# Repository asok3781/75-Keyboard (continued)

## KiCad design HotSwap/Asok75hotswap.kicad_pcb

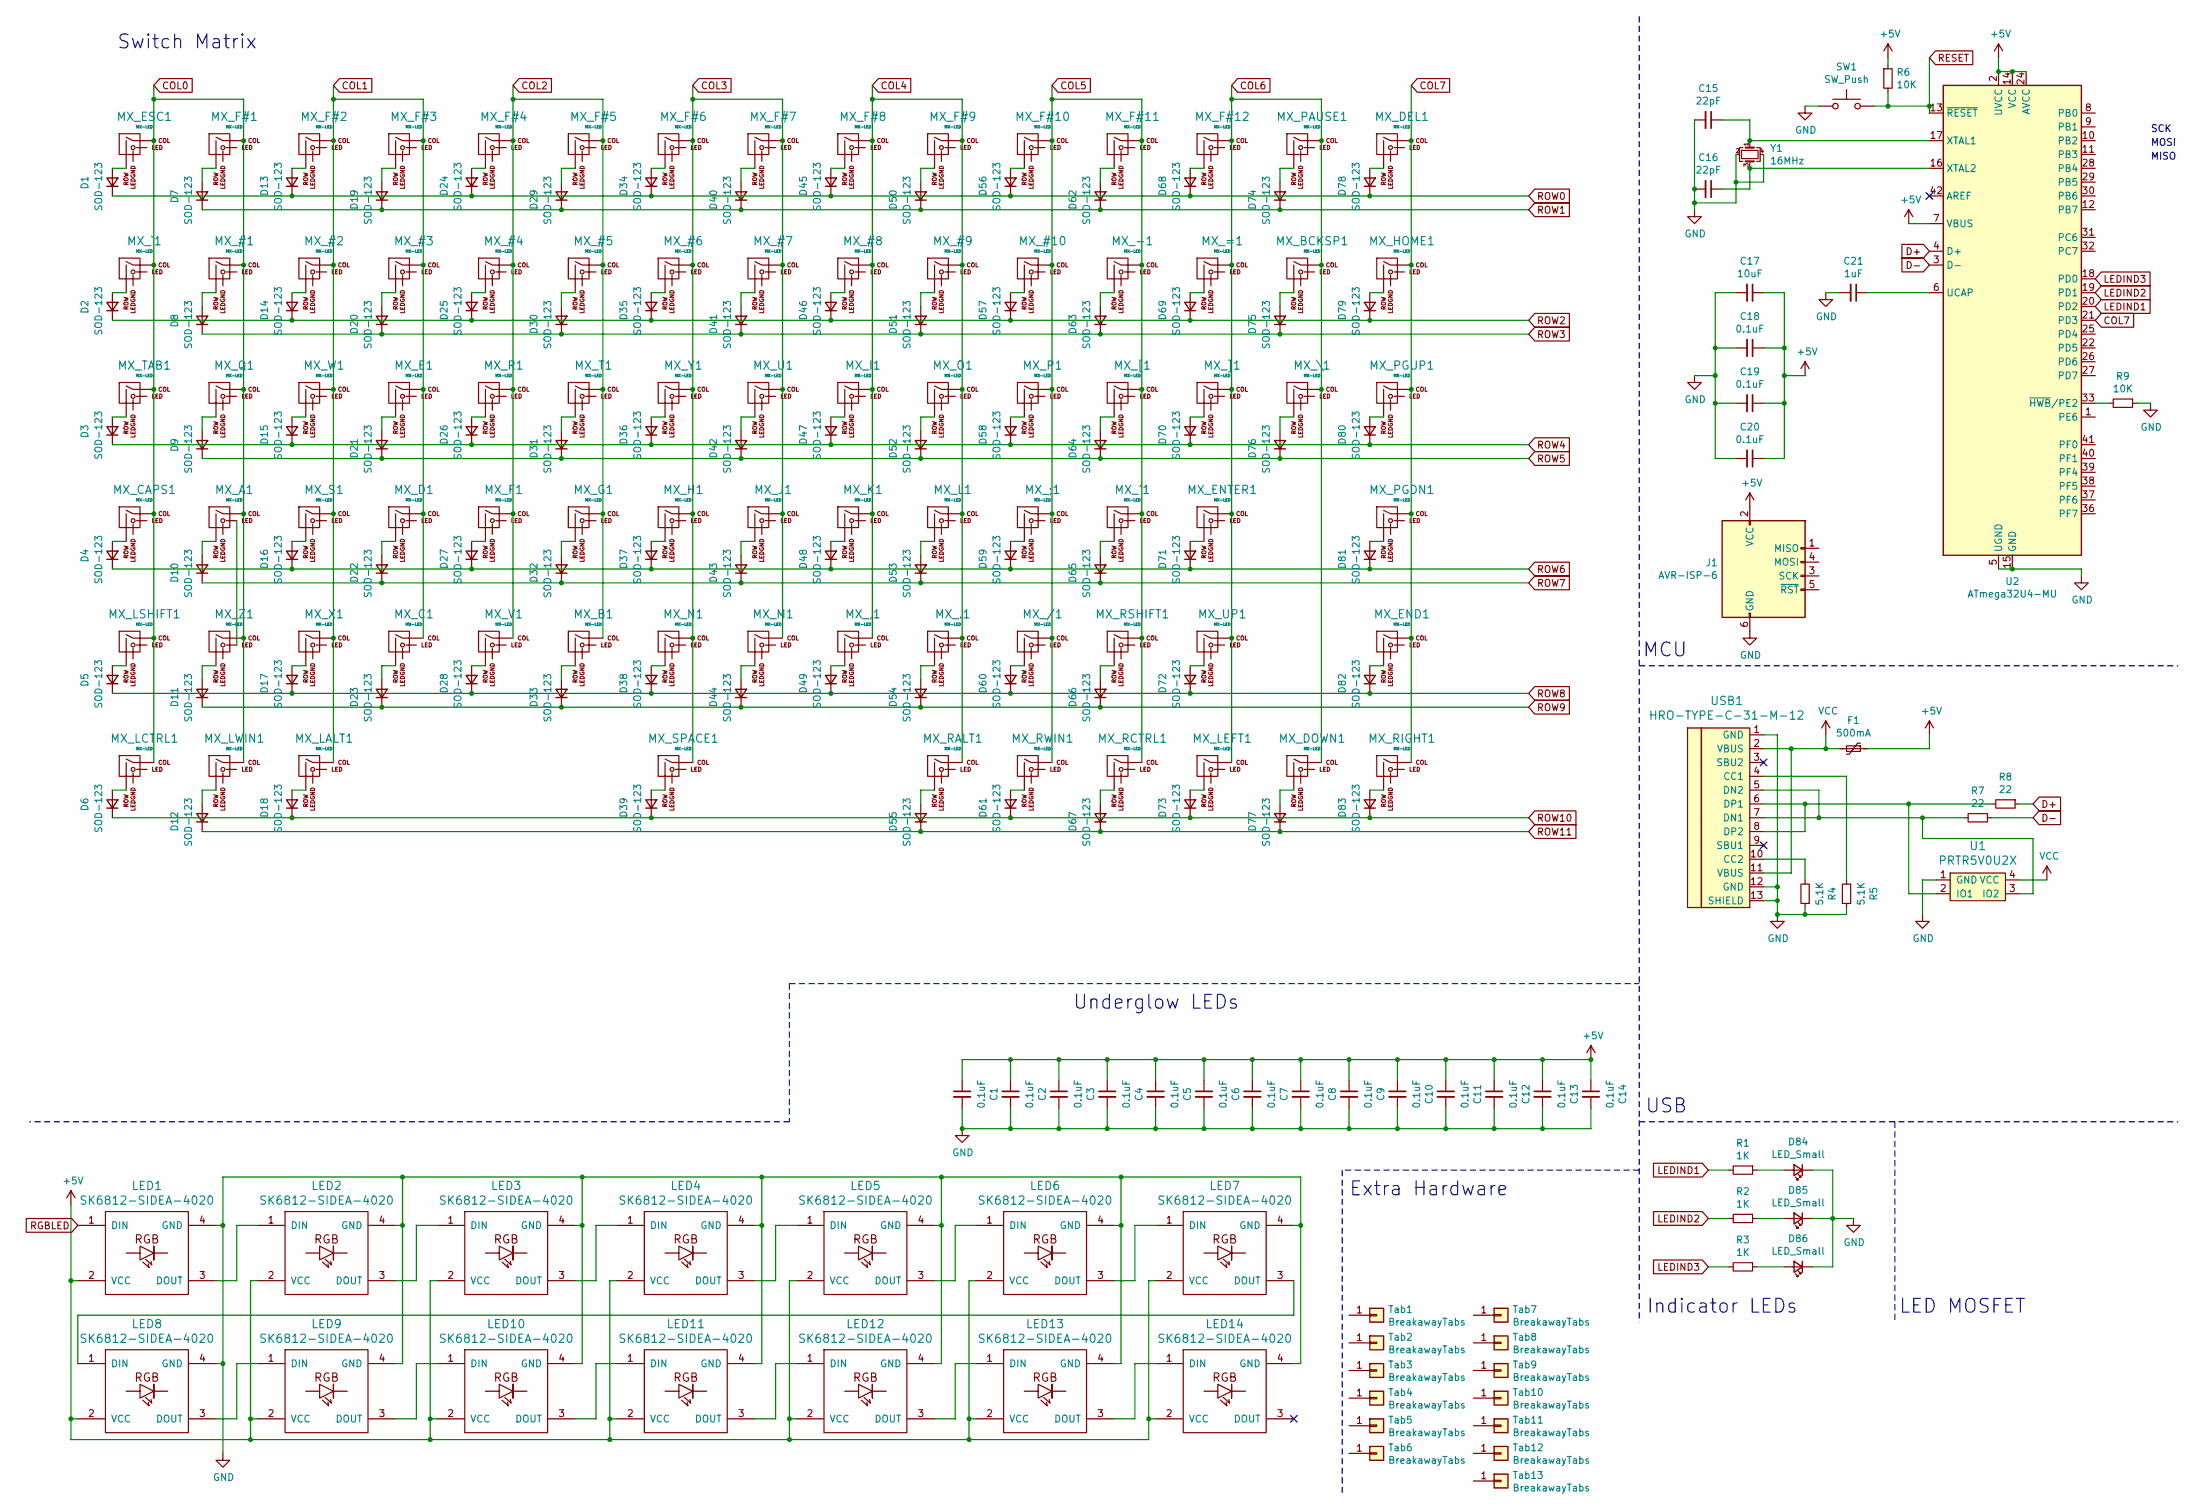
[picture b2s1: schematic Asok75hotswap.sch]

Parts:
C1, C2, C3, C4, C5, C6, C7, C8, C9, C10, C11, C12, C13, C14, C18, C19, C20: 0.1uF; C_0603_1608Metric
C15, C16: 22pF; C_0603_1608Metric
C17: 10uF; C_0603_1608Metric
C21: 1uF; C_0603_1608Metric
D1, D2, D3, D4, D5, D6, D7, D8, D9, D10, D11, D12, D13, D14, D15, D16, D17, D18, D19, D20, D21, D22, D23, D24, D25, D26, D27, D28, D29, D30, D31, D32, D33, D34, D35, D36, D37, D38, D39, D40, D41, D42, D43, D44, D45, D46, D47, D48, D49, D50, D51, D52, D53, D54, D55, D56, D57, D58, D59, D60, D61, D62, D63, D64, D65, D66, D67, D68, D69, D70, D71, D72, D73, D74, D75, D76, D77, D78, D79, D80, D81, D82, D83: SOD-123; D_SOD-123-Pretty
D84, D85, D86: LED_Small; LED_D3.0mm-Pretty
F1: 500mA; Fuse_1206_3216Metric
J1: AVR-ISP-6; Reset_Pretty-Mask
LED1, LED2, LED3, LED4, LED5, LED6, LED7, LED8, LED9, LED10, LED11, LED12, LED13, LED14: SK6812-SIDEA-4020
MX_#1, MX_#2, MX_#3, MX_#4, MX_#5, MX_#6, MX_#7, MX_#8, MX_#9, MX_#10: MX-LED; MXOnly-1U-Hotswap
MX_'1: MX-LED; MXOnly-1U-Hotswap
MX_,1: MX-LED; MXOnly-1U-Hotswap
MX_-1: MX-LED; MXOnly-1U-Hotswap
MX_.1: MX-LED; MXOnly-1U-Hotswap
MX_/1: MX-LED; MXOnly-1U-Hotswap
MX_;1: MX-LED; MXOnly-1U-Hotswap
MX_=1: MX-LED; MXOnly-1U-Hotswap
MX_A1: MX-LED; MXOnly-1U-Hotswap
MX_B1: MX-LED; MXOnly-1U-Hotswap
MX_BCKSP1: MX-LED; MXOnly-2U-Hotswap
MX_C1: MX-LED; MXOnly-1U-Hotswap
MX_CAPS1: MX-LED; MXOnly-1.75U-Hotswap
MX_D1: MX-LED; MXOnly-1U-Hotswap
MX_DEL1: MX-LED; MXOnly-1U-Hotswap
MX_DOWN1: MX-LED; MXOnly-1U-Hotswap
MX_E1: MX-LED; MXOnly-1U-Hotswap
MX_END1: MX-LED; MXOnly-1U-Hotswap
MX_ENTER1: MX-LED; MXOnly-2.25U-Hotswap-ReversedStabilizers
MX_ESC1: MX-LED; MXOnly-1U-Hotswap
MX_F1: MX-LED; MXOnly-1U-Hotswap
MX_F#1, MX_F#2, MX_F#3, MX_F#4, MX_F#5, MX_F#6, MX_F#7, MX_F#8, MX_F#9, MX_F#10, MX_F#11, MX_F#12: MX-LED; MXOnly-1U-Hotswap
MX_G1: MX-LED; MXOnly-1U-Hotswap
MX_H1: MX-LED; MXOnly-1U-Hotswap
MX_HOME1: MX-LED; MXOnly-1U-Hotswap
MX_I1: MX-LED; MXOnly-1U-Hotswap
MX_J1: MX-LED; MXOnly-1U-Hotswap
MX_K1: MX-LED; MXOnly-1U-Hotswap
MX_L1: MX-LED; MXOnly-1U-Hotswap
MX_LALT1: MX-LED; MXOnly-1.25U-Hotswap
MX_LCTRL1: MX-LED; MXOnly-1.25U-Hotswap
MX_LEFT1: MX-LED; MXOnly-1U-Hotswap
MX_LSHIFT1: MX-LED; MXOnly-2.25U-Hotswap
MX_LWIN1: MX-LED; MXOnly-1.25U-Hotswap
MX_M1: MX-LED; MXOnly-1U-Hotswap
MX_N1: MX-LED; MXOnly-1U-Hotswap
MX_O1: MX-LED; MXOnly-1U-Hotswap
MX_P1: MX-LED; MXOnly-1U-Hotswap
MX_PAUSE1: MX-LED; MXOnly-1U-Hotswap
MX_PGDN1: MX-LED; MXOnly-1U-Hotswap
MX_PGUP1: MX-LED; MXOnly-1U-Hotswap
MX_Q1: MX-LED; MXOnly-1U-Hotswap
MX_R1: MX-LED; MXOnly-1U-Hotswap
MX_RALT1: MX-LED; MXOnly-1U-Hotswap
MX_RCTRL1: MX-LED; MXOnly-1U-Hotswap
MX_RIGHT1: MX-LED; MXOnly-1U-Hotswap
MX_RSHIFT1: MX-LED; MXOnly-1.75U-Hotswap
MX_RWIN1: MX-LED; MXOnly-1U-Hotswap
MX_S1: MX-LED; MXOnly-1U-Hotswap
MX_SPACE1: MX-LED; MXOnly-6.25U-Hotswap-ReversedStabilizers
MX_T1: MX-LED; MXOnly-1U-Hotswap
MX_TAB1: MX-LED; MXOnly-1.5U-Hotswap
MX_U1: MX-LED; MXOnly-1U-Hotswap
MX_UP1: MX-LED; MXOnly-1U-Hotswap
MX_V1: MX-LED; MXOnly-1U-Hotswap
MX_W1: MX-LED; MXOnly-1U-Hotswap
MX_X1: MX-LED; MXOnly-1U-Hotswap
MX_Y1: MX-LED; MXOnly-1U-Hotswap
MX_Z1: MX-LED; MXOnly-1U-Hotswap
MX_[1: MX-LED; MXOnly-1U-Hotswap
MX_\1: MX-LED; MXOnly-1.5U-Hotswap
MX_]1: MX-LED; MXOnly-1U-Hotswap
MX_`1: MX-LED; MXOnly-1U-Hotswap
R1, R2, R3: 1K; R_0603_1608Metric
R4, R5: 5.1K; R_0603_1608Metric
R6, R9: 10K; R_0603_1608Metric
R7, R8: 22; R_0603_1608Metric
SW1: SW_Push; SKQG-1155865
Tab1, Tab2, Tab3, Tab4, Tab5, Tab6, Tab7, Tab8, Tab9, Tab10, Tab11, Tab12, Tab13: BreakawayTabs; breakaway-mousebites
U1: PRTR5V0U2X; SOT143B
U2: ATmega32U4-MU; QFN-44-1EP_7x7mm_P0.5mm_EP5.2x5.2mm
USB1: HRO-TYPE-C-31-M-12; HRO-TYPE-C-31-M-12-Assembly
Y1: 16MHz; Crystal_SMD_3225-4Pin_3.2x2.5mm

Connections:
+5V: C1.1, C2.1, C3.1, C4.1, C5.1, C6.1, C7.1, C8.1, C9.1, C10.1, C11.1, C12.1, C13.1, C14.1, C17.1, C18.1, C19.1, C20.1, F1.1, J1.2 (VCC), LED1.2 (VCC), LED2.2 (VCC), LED3.2 (VCC), LED4.2 (VCC), LED5.2 (VCC), LED6.2 (VCC), LED7.2 (VCC), LED8.2 (VCC), LED9.2 (VCC), LED10.2 (VCC), LED11.2 (VCC), LED12.2 (VCC), LED13.2 (VCC), LED14.2 (VCC), R6.1, U2.2 (UVCC), U2.7 (VBUS), U2.14 (VCC), U2.24 (AVCC), U2.34 (VCC), U2.44 (AVCC)
COL0: MX_#1.1 (COL), MX_A1.1 (COL), MX_CAPS1.1 (COL), MX_ESC1.1 (COL), MX_F#1.1 (COL), MX_LCTRL1.1 (COL), MX_LSHIFT1.1 (COL), MX_LWIN1.1 (COL), MX_Q1.1 (COL), MX_TAB1.1 (COL), MX_Z1.1 (COL), MX_`1.1 (COL)
COL1: MX_#2.1 (COL), MX_#3.1 (COL), MX_C1.1 (COL), MX_D1.1 (COL), MX_E1.1 (COL), MX_F#2.1 (COL), MX_F#3.1 (COL), MX_LALT1.1 (COL), MX_S1.1 (COL), MX_W1.1 (COL), MX_X1.1 (COL)
COL2: MX_#4.1 (COL), MX_#5.1 (COL), MX_B1.1 (COL), MX_F1.1 (COL), MX_F#4.1 (COL), MX_F#5.1 (COL), MX_G1.1 (COL), MX_R1.1 (COL), MX_T1.1 (COL), MX_V1.1 (COL)
COL3: MX_#6.1 (COL), MX_#7.1 (COL), MX_F#6.1 (COL), MX_F#7.1 (COL), MX_H1.1 (COL), MX_J1.1 (COL), MX_M1.1 (COL), MX_N1.1 (COL), MX_SPACE1.1 (COL), MX_U1.1 (COL), MX_Y1.1 (COL)
COL4: MX_#8.1 (COL), MX_#9.1 (COL), MX_,1.1 (COL), MX_.1.1 (COL), MX_F#8.1 (COL), MX_F#9.1 (COL), MX_I1.1 (COL), MX_K1.1 (COL), MX_L1.1 (COL), MX_O1.1 (COL), MX_RALT1.1 (COL)
COL5: MX_#10.1 (COL), MX_'1.1 (COL), MX_-1.1 (COL), MX_/1.1 (COL), MX_;1.1 (COL), MX_F#10.1 (COL), MX_F#11.1 (COL), MX_P1.1 (COL), MX_RCTRL1.1 (COL), MX_RSHIFT1.1 (COL), MX_RWIN1.1 (COL), MX_[1.1 (COL)
COL6: MX_=1.1 (COL), MX_BCKSP1.1 (COL), MX_DOWN1.1 (COL), MX_ENTER1.1 (COL), MX_F#12.1 (COL), MX_LEFT1.1 (COL), MX_PAUSE1.1 (COL), MX_UP1.1 (COL), MX_\1.1 (COL), MX_]1.1 (COL)
COL7: MX_DEL1.1 (COL), MX_END1.1 (COL), MX_HOME1.1 (COL), MX_PGDN1.1 (COL), MX_PGUP1.1 (COL), MX_RIGHT1.1 (COL), U2.21 (PD3)
D+: R8.1, U2.4 (D+)
D-: R7.1, U2.3 (D-)
GND: C1.2, C2.2, C3.2, C4.2, C5.2, C6.2, C7.2, C8.2, C9.2, C10.2, C11.2, C12.2, C13.2, C14.2, C15.2, C16.2, C17.2, C18.2, C19.2, C20.2, C21.2, D84.1 (K), D85.1 (K), D86.1 (K), J1.6 (GND), LED1.4 (GND), LED2.4 (GND), LED3.4 (GND), LED4.4 (GND), LED5.4 (GND), LED6.4 (GND), LED7.4 (GND), LED8.4 (GND), LED9.4 (GND), LED10.4 (GND), LED11.4 (GND), LED12.4 (GND), LED13.4 (GND), LED14.4 (GND), R4.1, R5.1, R9.1, SW1.1, U1.1 (GND), U2.5 (UGND), U2.15 (GND), U2.23 (GND), U2.35 (GND), U2.43 (GND), U2.45 (GND), USB1.1 (GND), USB1.12 (GND), USB1.13 (SHIELD), Y1.2, Y1.4
LEDIND1: R1.2, U2.20 (PD2)
LEDIND2: R2.2, U2.19 (PD1)
LEDIND3: R3.2, U2.18 (PD0)
unnamed: C15.1, U2.17 (XTAL1), Y1.1
unnamed: C16.1, U2.16 (XTAL2), Y1.3
unnamed: C21.1, U2.6 (UCAP)
unnamed: D1.2 (A), MX_ESC1.2 (ROW)
unnamed: D2.2 (A), MX_`1.2 (ROW)
unnamed: D3.2 (A), MX_TAB1.2 (ROW)
unnamed: D4.2 (A), MX_CAPS1.2 (ROW)
unnamed: D5.2 (A), MX_LSHIFT1.2 (ROW)
unnamed: D6.2 (A), MX_LCTRL1.2 (ROW)
unnamed: D7.2 (A), MX_F#1.2 (ROW)
unnamed: D8.2 (A), MX_#1.2 (ROW)
unnamed: D9.2 (A), MX_Q1.2 (ROW)
unnamed: D10.2 (A), MX_A1.2 (ROW)
unnamed: D11.2 (A), MX_Z1.2 (ROW)
unnamed: D12.2 (A), MX_LWIN1.2 (ROW)
unnamed: D13.2 (A), MX_F#2.2 (ROW)
unnamed: D14.2 (A), MX_#2.2 (ROW)
unnamed: D15.2 (A), MX_W1.2 (ROW)
unnamed: D16.2 (A), MX_S1.2 (ROW)
unnamed: D17.2 (A), MX_X1.2 (ROW)
unnamed: D18.2 (A), MX_LALT1.2 (ROW)
unnamed: D19.2 (A), MX_F#3.2 (ROW)
unnamed: D20.2 (A), MX_#3.2 (ROW)
unnamed: D21.2 (A), MX_E1.2 (ROW)
unnamed: D22.2 (A), MX_D1.2 (ROW)
unnamed: D23.2 (A), MX_C1.2 (ROW)
unnamed: D24.2 (A), MX_F#4.2 (ROW)
unnamed: D25.2 (A), MX_#4.2 (ROW)
unnamed: D26.2 (A), MX_R1.2 (ROW)
unnamed: D27.2 (A), MX_F1.2 (ROW)
unnamed: D28.2 (A), MX_V1.2 (ROW)
unnamed: D29.2 (A), MX_F#5.2 (ROW)
unnamed: D30.2 (A), MX_#5.2 (ROW)
unnamed: D31.2 (A), MX_T1.2 (ROW)
unnamed: D32.2 (A), MX_G1.2 (ROW)
unnamed: D33.2 (A), MX_B1.2 (ROW)
unnamed: D34.2 (A), MX_F#6.2 (ROW)
unnamed: D35.2 (A), MX_#6.2 (ROW)
unnamed: D36.2 (A), MX_Y1.2 (ROW)
unnamed: D37.2 (A), MX_H1.2 (ROW)
unnamed: D38.2 (A), MX_N1.2 (ROW)
unnamed: D39.2 (A), MX_SPACE1.2 (ROW)
unnamed: D40.2 (A), MX_F#7.2 (ROW)
unnamed: D41.2 (A), MX_#7.2 (ROW)
unnamed: D42.2 (A), MX_U1.2 (ROW)
unnamed: D43.2 (A), MX_J1.2 (ROW)
unnamed: D44.2 (A), MX_M1.2 (ROW)
unnamed: D45.2 (A), MX_F#8.2 (ROW)
unnamed: D46.2 (A), MX_#8.2 (ROW)
unnamed: D47.2 (A), MX_I1.2 (ROW)
unnamed: D48.2 (A), MX_K1.2 (ROW)
unnamed: D49.2 (A), MX_,1.2 (ROW)
unnamed: D50.2 (A), MX_F#9.2 (ROW)
unnamed: D51.2 (A), MX_#9.2 (ROW)
unnamed: D52.2 (A), MX_O1.2 (ROW)
unnamed: D53.2 (A), MX_L1.2 (ROW)
unnamed: D54.2 (A), MX_.1.2 (ROW)
unnamed: D55.2 (A), MX_RALT1.2 (ROW)
unnamed: D56.2 (A), MX_F#10.2 (ROW)
unnamed: D57.2 (A), MX_#10.2 (ROW)
unnamed: D58.2 (A), MX_P1.2 (ROW)
unnamed: D59.2 (A), MX_;1.2 (ROW)
unnamed: D60.2 (A), MX_/1.2 (ROW)
unnamed: D61.2 (A), MX_RWIN1.2 (ROW)
unnamed: D62.2 (A), MX_F#11.2 (ROW)
unnamed: D63.2 (A), MX_-1.2 (ROW)
unnamed: D64.2 (A), MX_[1.2 (ROW)
unnamed: D65.2 (A), MX_'1.2 (ROW)
unnamed: D66.2 (A), MX_RSHIFT1.2 (ROW)
unnamed: D67.2 (A), MX_RCTRL1.2 (ROW)
unnamed: D68.2 (A), MX_F#12.2 (ROW)
unnamed: D69.2 (A), MX_=1.2 (ROW)
unnamed: D70.2 (A), MX_]1.2 (ROW)
unnamed: D71.2 (A), MX_ENTER1.2 (ROW)
unnamed: D72.2 (A), MX_UP1.2 (ROW)
unnamed: D73.2 (A), MX_LEFT1.2 (ROW)
unnamed: D74.2 (A), MX_PAUSE1.2 (ROW)
unnamed: D75.2 (A), MX_BCKSP1.2 (ROW)
unnamed: D76.2 (A), MX_\1.2 (ROW)
unnamed: D77.2 (A), MX_DOWN1.2 (ROW)
unnamed: D78.2 (A), MX_DEL1.2 (ROW)
unnamed: D79.2 (A), MX_HOME1.2 (ROW)
unnamed: D80.2 (A), MX_PGUP1.2 (ROW)
unnamed: D81.2 (A), MX_PGDN1.2 (ROW)
unnamed: D82.2 (A), MX_END1.2 (ROW)
unnamed: D83.2 (A), MX_RIGHT1.2 (ROW)
unnamed: D84.2 (A), R1.1
unnamed: D85.2 (A), R2.1
unnamed: D86.2 (A), R3.1
unnamed: LED1.3 (DOUT), LED2.1 (DIN)
unnamed: LED2.3 (DOUT), LED3.1 (DIN)
unnamed: LED3.3 (DOUT), LED4.1 (DIN)
unnamed: LED4.3 (DOUT), LED5.1 (DIN)
unnamed: LED5.3 (DOUT), LED6.1 (DIN)
unnamed: LED6.3 (DOUT), LED7.1 (DIN)
unnamed: LED7.3 (DOUT), LED8.1 (DIN)
unnamed: LED8.3 (DOUT), LED9.1 (DIN)
unnamed: LED9.3 (DOUT), LED10.1 (DIN)
unnamed: LED10.3 (DOUT), LED11.1 (DIN)
unnamed: LED11.3 (DOUT), LED12.1 (DIN)
unnamed: LED12.3 (DOUT), LED13.1 (DIN)
unnamed: LED13.3 (DOUT), LED14.1 (DIN)
unnamed: R4.2, USB1.10 (CC2)
unnamed: R5.2, USB1.4 (CC1)
unnamed: R7.2, U1.3 (IO2), USB1.5 (DN2), USB1.7 (DN1)
unnamed: R8.2, U1.2 (IO1), USB1.6 (DP1), USB1.8 (DP2)
unnamed: R9.2, U2.33 (~HWB~/PE2)
RESET: R6.2, SW1.2, U2.13 (~RESET)
RGBLED: LED1.1 (DIN)
ROW0: D1.1 (K), D13.1 (K), D24.1 (K), D34.1 (K), D45.1 (K), D56.1 (K), D68.1 (K), D78.1 (K)
ROW1: D7.1 (K), D19.1 (K), D29.1 (K), D40.1 (K), D50.1 (K), D62.1 (K), D74.1 (K)
ROW2: D2.1 (K), D14.1 (K), D25.1 (K), D35.1 (K), D46.1 (K), D57.1 (K), D69.1 (K), D79.1 (K)
ROW3: D8.1 (K), D20.1 (K), D30.1 (K), D41.1 (K), D51.1 (K), D63.1 (K), D75.1 (K)
ROW4: D3.1 (K), D15.1 (K), D26.1 (K), D36.1 (K), D47.1 (K), D58.1 (K), D70.1 (K), D80.1 (K)
ROW5: D9.1 (K), D21.1 (K), D31.1 (K), D42.1 (K), D52.1 (K), D64.1 (K), D76.1 (K)
ROW6: D4.1 (K), D16.1 (K), D27.1 (K), D37.1 (K), D48.1 (K), D59.1 (K), D71.1 (K), D81.1 (K)
ROW7: D10.1 (K), D22.1 (K), D32.1 (K), D43.1 (K), D53.1 (K), D65.1 (K)
ROW8: D5.1 (K), D17.1 (K), D28.1 (K), D38.1 (K), D49.1 (K), D60.1 (K), D72.1 (K), D82.1 (K)
ROW9: D11.1 (K), D23.1 (K), D33.1 (K), D44.1 (K), D54.1 (K), D66.1 (K)
ROW10: D6.1 (K), D18.1 (K), D39.1 (K), D61.1 (K), D73.1 (K), D83.1 (K)
ROW11: D12.1 (K), D55.1 (K), D67.1 (K), D77.1 (K)
VCC: F1.2, U1.4 (VCC), USB1.2 (VBUS), USB1.11 (VBUS)

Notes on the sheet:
MCU
USB
Indicator LEDs
Switch Matrix
LED MOSFET
Underglow LEDs
SCK
MOSI
MISO
Extra Hardware

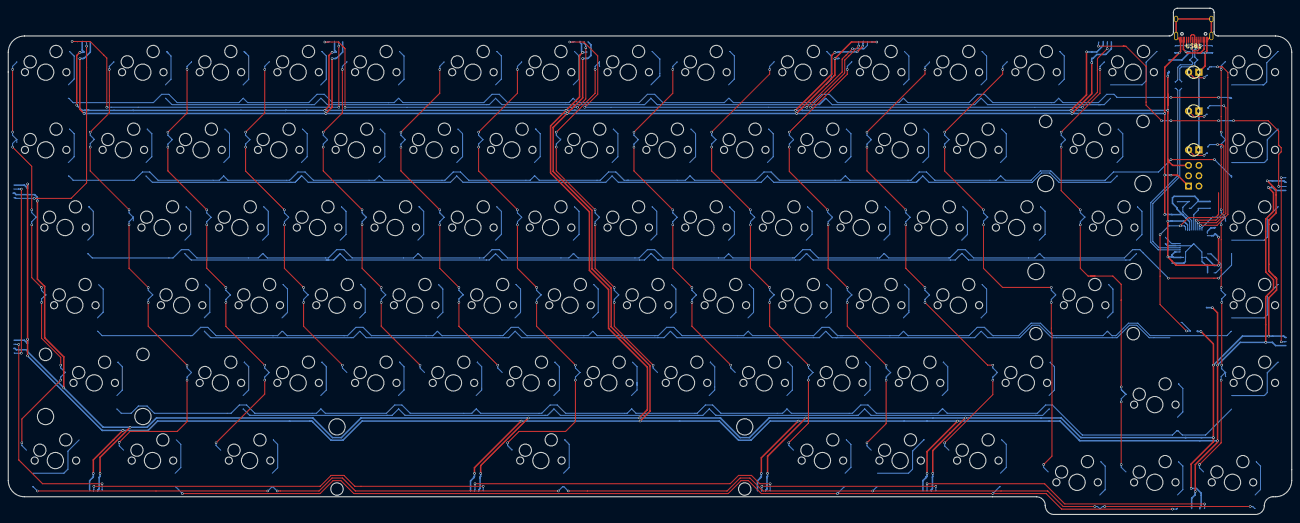
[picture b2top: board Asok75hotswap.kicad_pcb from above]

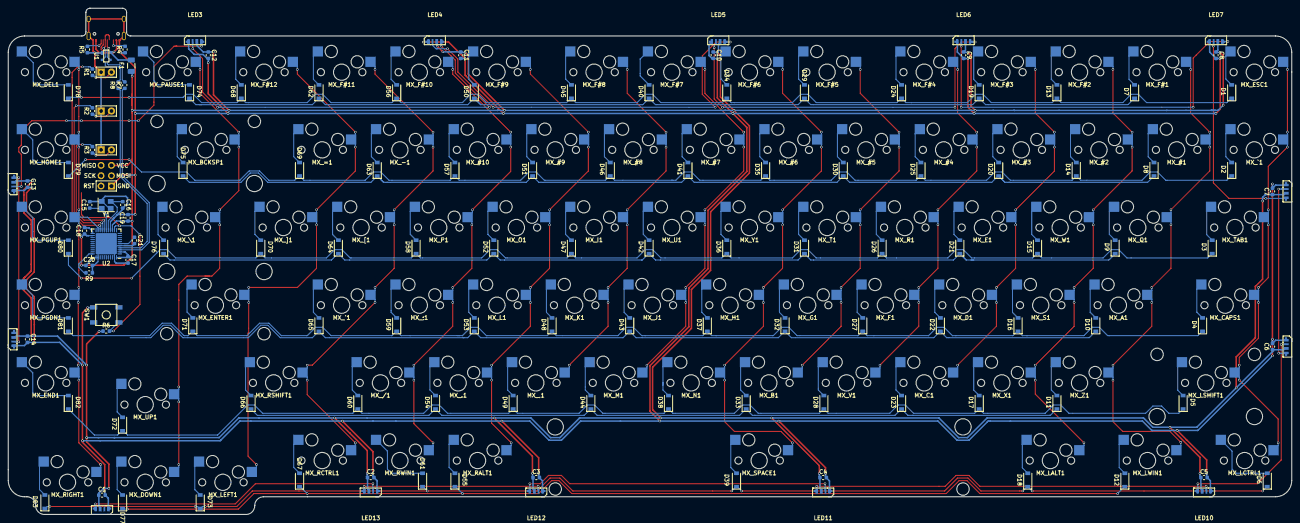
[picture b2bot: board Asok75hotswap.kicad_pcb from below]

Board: 2 copper layers, 314.8 x 124.1 mm, 233 parts (133 on the bottom side), 136 nets.

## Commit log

2020-03-29 Initialised project
2020-03-29 Added submodules for keyboard part footprints
2020-03-29 Added footprint libraries
2020-03-29 Added submodule for USB Type-C footprints
2020-03-29 Finished MCU schematic
2020-03-29 Finished USB schematic
2020-03-29 Finished placing switch symbols
2020-03-29 Finished columns in switch matrix
2020-03-30 Finished switch matrix schematic
2020-03-30 Added Schottky diode
2020-03-30 Changed switches to support LEDs
2020-03-31 Changed MCU from ATmega32U4 to AT90USB1286 for more pins
2020-03-31 Added ISP to schematic
2020-03-31 Changed layout of switch matrix in schematic
2020-04-01 Created copy of schematic for hot-swap implementation, added diodes and an extra switch symbol for split backspace support
2020-04-01 Added switch for split right shift support
2020-04-02 Added switches for multiple layouts
2020-04-02 Added switches for modifiers for 7U spacebar
2020-04-02 Finished LED backlight matrix
2020-04-04 Added submodule for RGB LEDs
2020-04-04 Added Underglow LEDs
2020-04-06 Added switches for JIS bottom row
2020-04-06 Assigned footprints
2020-04-07 Added switch for support for another bottom row layout
2020-04-07 Finished key layout in PCB file
2020-04-07 Finished PCB edges
2020-04-07 Changed USB connector
2020-04-14 Positioned underglow LEDs
2020-04-15 Updated switch footprints
2020-04-17 Finished MCU capacitor and USB traces
2020-04-17 Placed LED resistors
2020-04-17 Finished switch and LED matrix traces
2020-04-18 Reset traces, changed component placement
2020-04-18 Finished USB and 5V traces
2020-04-18 Fixed underglow LED schematic and switch footprints
2020-04-19 Finished row and LED ground traces
2020-04-19 Finished column traces
2020-04-19 Finished column and LED traces
2020-04-19 Finished LED matrix
2020-04-20 Created duplex matrix for switches and switched MCU to ATMega32U4
2020-04-20 Finished USB and MCU traces
2020-04-20 Finished column and row traces
2020-04-21 Updated underglow LED placement
2020-04-21 Changed underglow LED model
2020-04-21 Finished routing traces around underglow LEDs
2020-04-22 Added mounting holes
2020-04-22 Finished traces and added ground fills
2020-04-23 Adjusted silkscreen and added edge rails
2020-04-23 Cleaned up schematic
2020-04-24 Changed power trace width
2020-04-24 Connected unconnected pad
2020-04-24 Updated switch matrix
2020-04-25 Added graphics
2020-04-26 Renamed project
2020-07-06 Added files for acrylic case
2020-07-08 Updated case files
2020-07-19 Added README.md for case files
2020-07-21 Create LICENSE
2020-08-03 Deleted traces, updated dimensions, added new symbols and footprints for side firing underglow LEDS
2020-08-04 Reorganised folders and placed RGB LEDs on hotswap pcb
2020-08-11 Removed extra symbols in schematic in hotswap variant
2020-08-12 Updated PCB dimensions and component placement on hotswap variant
2020-08-14 Updated underglow LED footprint
2020-08-17 Routed USB and MCU area for hotswap version
2020-08-18 Updated edge cuts
2020-08-18 Realigned underglow LEDs
2020-08-18 Updated hotswap PCB
2020-08-19 Completed routing rows, MCU and USB
2020-08-19 Finished routing columns in hotswap version
2020-08-20 Routed underglow LEDs
2020-08-20 Finished routing underglow LED power traces
2020-08-22 Finished routing hotswap version
2020-09-04 Update README.md
    Added 2 images of the board
2020-09-04 Fixed the image links of the keyboard
2020-09-12 Moved case folder to be with v1 PCB
2020-09-21 Refactored project into separate repositories
2020-09-21 Added VIA definition to repository
